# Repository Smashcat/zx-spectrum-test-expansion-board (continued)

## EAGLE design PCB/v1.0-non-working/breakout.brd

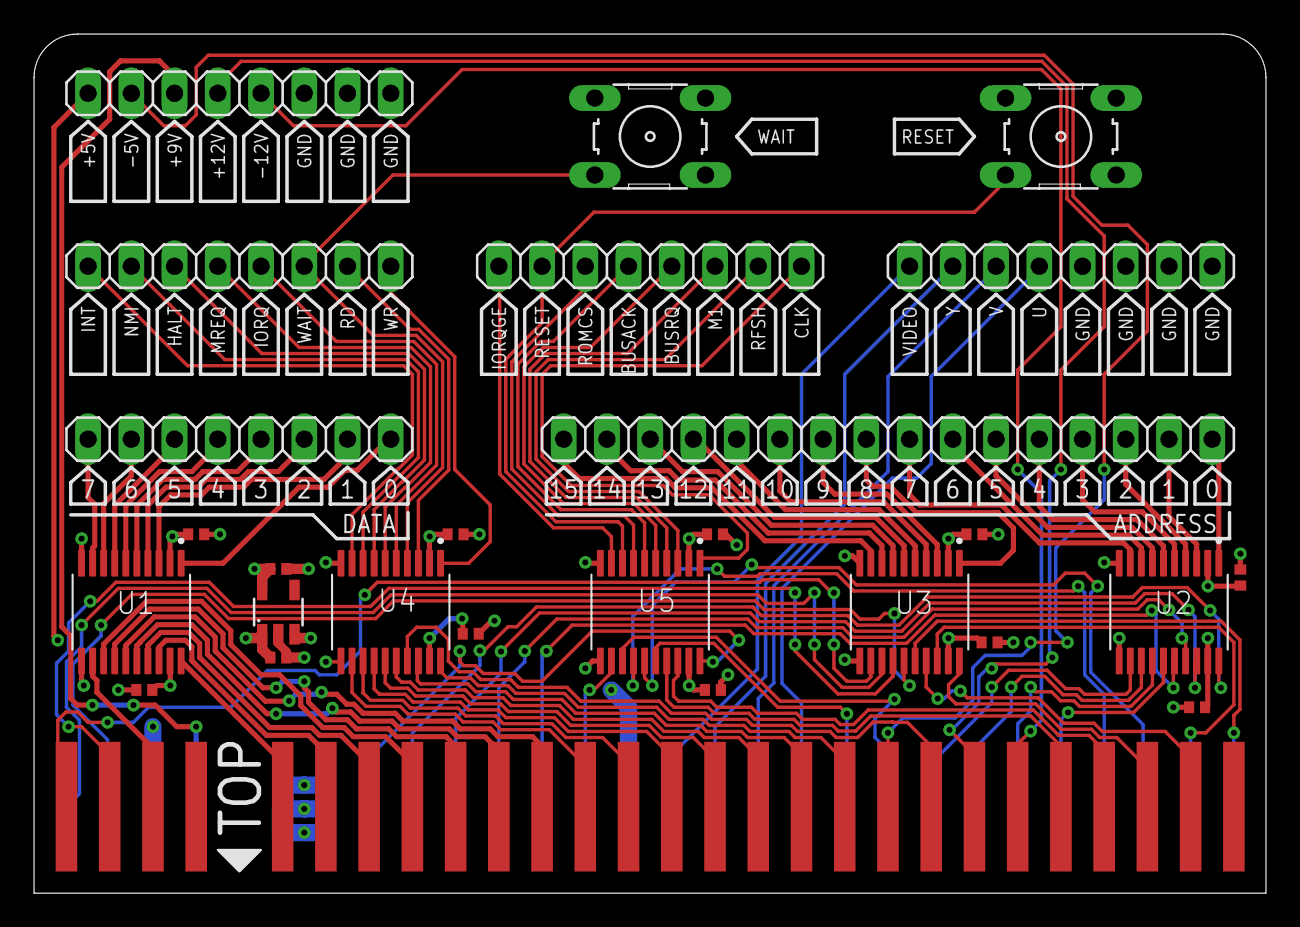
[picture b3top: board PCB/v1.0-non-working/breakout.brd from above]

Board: 4 copper layers, 72.4 x 50.5 mm, 27 parts (0 on the bottom side), 91 nets.

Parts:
3V3_REG4: 3V3; NCP718BSN330T1G
C1, C2, C3, C4, C5, C6, C7, C8, C9, C10: 100nF; C0402
C34, C35: 1uF; C0402
JP1, JP3, JP4, JP5, JP7: 1X08
JP2: 1X16
RESET_BUTTON: B3F-10XX-3D
U1, U2, U3, U4, U5: TXB0108PWR; SOP65P640X120-20N
U$1: ZX-SPECTRUM-EDGE-CONNECTOR
WAIT_BUTTON: B3F-10XX-3D

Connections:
3V3: 3V3_REG4.5, C1.1, C3.1, C5.1, C7.1, C9.1, C35.1, U1.2, U1.10, U2.2, U2.10, U3.2, U3.10, U4.2, U4.10, U5.2, U5.10
+5V: 3V3_REG4.1, 3V3_REG4.3, C2.1, C4.1, C6.1, C8.1, C10.1, C34.1, JP3.1, U1.19, U2.19, U3.19, U4.19, U5.19, U$1.B3
+9V: JP3.3, U$1.B4
+12V: JP3.4, U$1.A22
-5V: JP3.2, U$1.A20
-12V: JP3.5, U$1.A23
/BUSACK: U5.15, U$1.B26
/BUSACK_LOW: JP4.5, U5.6
/BUSRQ: U5.16, U$1.B19
/BUSRQ_LOW: JP4.4, U5.5
/HALT: U4.14, U$1.A15
/HALT_LOW: JP7.6, U4.7
/INT: U4.12, U$1.A13
/INT_LOW: JP7.8, U4.9
/IORQ: U4.16, U$1.A17
/IORQGE: U5.12, U$1.B13
/IORQGE_LOW: JP4.8, U5.9
/IORQ_LOW: JP7.4, U4.5
/M1: U5.17, U$1.A24
/M1_LOW: JP4.3, U5.4
/MREQ: U4.15, U$1.A16
/MREQ_LOW: JP7.5, U4.6
/NMI: U4.13, U$1.A14
/NMI_LOW: JP7.7, U4.8
/RD: U4.18, U$1.A18
/RD_LOW: JP7.2, U4.3
/RESET: U5.13, U$1.B20
/RESET_LOW: JP4.7, RESET_BUTTON.3, U5.8
/RFSH: U5.18, U$1.A25
/RFSH_LOW: JP4.2, U5.3
/ROMCS: U5.14, U$1.B25
/ROMCS_LOW: JP4.6, U5.7
/WAIT: U4.17, U$1.A21
/WAIT_LOW: JP7.3, U4.4, WAIT_BUTTON.3
/WR: U4.20, U$1.A19
/WR_LOW: JP7.1, U4.1
A0: U2.20, U$1.B9
A0_LOW: JP2.1, U2.1
A1: U2.18, U$1.B10
A1_LOW: JP2.2, U2.3
A2: U2.17, U$1.B11
A2_LOW: JP2.3, U2.4
A3: U2.16, U$1.B12
A3_LOW: JP2.4, U2.5
A4: U2.15, U$1.B24
A4_LOW: JP2.5, U2.6
A5: U2.14, U$1.B23
A5_LOW: JP2.6, U2.7
A6: U2.13, U$1.B22
A6_LOW: JP2.7, U2.8
A7: U2.12, U$1.B21
A7_LOW: JP2.8, U2.9
A8: U3.20, U$1.A26
A8_LOW: JP2.9, U3.1
A9: U3.18, U$1.B27
A9_LOW: JP2.10, U3.3
A10: U3.17, U$1.A27
A10_LOW: JP2.11, U3.4
A11: U3.16, U$1.B28
A11_LOW: JP2.12, U3.5
A12: U3.15, U$1.B2
A12_LOW: JP2.13, U3.6
A13: U3.14, U$1.A2
A13_LOW: JP2.14, U3.7
A14: U3.13, U$1.B1
A14_LOW: JP2.15, U3.8
A15: U3.12, U$1.A1
A15_LOW: JP2.16, U3.9
CLK: U5.20, U$1.B8
CLK_LOW: JP4.1, U5.1
D0: U1.20, U$1.A6
D0_LOW: JP1.1, U1.1
D1: U1.18, U$1.A7
D1_LOW: JP1.2, U1.3
D2: U1.17, U$1.A8
D2_LOW: JP1.3, U1.4
D3: U1.16, U$1.A11
D3_LOW: JP1.4, U1.5
D4: U1.15, U$1.A12
D4_LOW: JP1.5, U1.6
D5: U1.14, U$1.A10
D5_LOW: JP1.6, U1.7
D6: U1.13, U$1.A9
D6_LOW: JP1.7, U1.8
D7: U1.12, U$1.A3
D7_LOW: JP1.8, U1.9
GND: 3V3_REG4.2, C1.2, C2.2, C3.2, C4.2, C5.2, C6.2, C7.2, C8.2, C9.2, C10.2, C34.2, C35.2, JP3.6, JP3.7, JP3.8, JP5.5, JP5.6, JP5.7, JP5.8, RESET_BUTTON.1, U1.11, U2.11, U3.11, U4.11, U5.11, U$1.B6, U$1.B7, U$1.B14, WAIT_BUTTON.1
U: JP5.4, U$1.B18
V: JP5.3, U$1.B17
VIDEO: JP5.1, U$1.B15
Y: JP5.2, U$1.B16

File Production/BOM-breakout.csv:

Qty,Designator,Footprint,Comment,LCSC Part #,Description,Device
10,"C1, C2, C3, C4, C5, C6, C7, C8, C9, C10",C0402,100nF,C307331,"CAPACITOR, European symbol",C-EUC0402
2,"C34, C35",C0402,1uF,C52923,"CAPACITOR, European symbol",C-EUC0402
1,3V3_REG4,NCP718BSN330T1G,3V3,C587158,,NCP718BSN330T1G
5,"U1, U2, U3, U4, U5",SOP65P640X120-20N,TXB0108PWR,C17206,8-Bit Bidirectional Voltage-Level Shifter with Auto Direction Sensing and +/-15-kV ESD Protect 20-TSSOP -40 to 85  Check availability,TXB0108PWR

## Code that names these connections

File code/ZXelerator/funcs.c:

#include "funcs.h"
#include "resetData.h"

PIO pio;
uint addr_data_sm;

void setupIO(void){
        // -------------------------------
    // set-up user, romcs & reset gpio
    // -------------------------------
    gpio_init(PIN_RESET);
    gpio_set_dir(PIN_RESET,GPIO_OUT);
    gpio_put(PIN_RESET,false);    // initially not in RESET, as we need to wait for at least one memory access so that the PIO will work correctly
    //
    gpio_init(PIN_USER);
    gpio_set_dir(PIN_USER,GPIO_OUT);
    gpio_put(PIN_USER,true); // button active when connected to ground
    gpio_set_irq_enabled_with_callback(PIN_USER,GPIO_IRQ_EDGE_FALL,true,&resetButton);  // when user button pressed, interrupt code and run resetButton routine
    //
    gpio_init(PIN_ROMCS);
    gpio_set_dir(PIN_ROMCS,GPIO_OUT);
    gpio_put(PIN_ROMCS,false);    // start with ROM off  
    //
    gpio_init(PIN_LED);
    gpio_set_dir(PIN_LED,GPIO_OUT);
    gpio_put(PIN_LED,false);

    // Initialise the ASM data banks
    for(int n=0;n<3;n++){
        copyBank(ram[n][0],resetBank[0]);
    }
}

void setupPIO(void){
    // Set-up PIO
    pio=pio0;                                                           // use pio 0
    addr_data_sm=pio_claim_unused_sm(pio,true);                         // grab a free state machine from PIO 0
    uint addr_data_offset=pio_add_program(pio,&picoif2_program);        // get instruction memory offset for the loaded program
    pio_sm_config addr_data_config=picoif2_program_get_default_config(addr_data_offset); // get the default state machine config

    // set-up IN pins
    for(uint i=PIN_A0;i<PIN_A0+14;i++) {
        pio_gpio_init(pio,i);                                           // initialise all 14 input pins 
    }    
    pio_sm_set_consecutive_pindirs(pio,addr_data_sm,PIN_A0,14,false);   // input
    sm_config_set_in_pins(&addr_data_config,PIN_A0);                    // set IN pin base
    sm_config_set_in_shift(&addr_data_config,false,true,14);            // shift left 14 pins (A13-A0) into ISR, autopush resultant 32bit address to DMA RXF

    // set-up /ROMRQ pin
    pio_gpio_init(pio,PIN_ROMRQ);                                       // ROMRQ (OR of A14,A15 and /MREQ lines) When this switches to LOW it triggers the address line input DMA transfer
    pio_sm_set_consecutive_pindirs(pio,addr_data_sm,PIN_ROMRQ,1,false); // input
    
    // set-up OUT pins
    for(uint i=PIN_D0;i<PIN_D0+8;i++) {                                 // set-up OUT data pins
        pio_gpio_init(pio,i);                                           // initialise all 8 output pins
    }
    sm_config_set_out_pins(&addr_data_config,PIN_D0,8);                 // set OUT pin base & number (bits)
    sm_config_set_out_shift(&addr_data_config,true,true,8);             // right shift 8 bits of OSR to pins (D0-D7) with autopull on
    pio_sm_set_consecutive_pindirs(pio,addr_data_sm,PIN_D0,8,true);     // set all output pins to output, D0-D7
    pio_sm_init(pio,addr_data_sm,addr_data_offset,&addr_data_config);   // reset state machine and configure it

    // start PIO state machine
    pio_sm_set_enabled(pio,addr_data_sm,true);                          // enable state machine       
}

void releaseReset(void){
    busy_wait_us_32(50000);      // wait 50ms before lifting RESET          
    gpio_put(PIN_RESET,true);    // release RESET    
}

void __not_in_flash_func(handleZ80Read)(void){
    uint32_t bank1SwapCnt=0;
    uint32_t keyScanCnt=0;
    uint32_t currentSubBank=0;
    int haltCD=0;
    const uint8_t *readPtr=ram[readBank][currentSubBank];
    
    enableROMOutput();
    gpio_put(PIN_RESET,true);   // lift reset
    while(true){
        while((pio->fstat & (1u << (PIO_FSTAT_RXEMPTY_LSB + addr_data_sm))) != 0);
        uint32_t address=pio->rxf[addr_data_sm];
        //uint32_t address=pio_sm_get_blocking(pio,addr_data_sm);
        pio->txf[addr_data_sm] = *(readPtr+address);
        //pio_sm_put_blocking(pio,addr_data_sm,*(readPtr+address)); // if ROMCS off then direction of Data chip is input so they do not interfere
        writeOK=1;
        if((address==0x3fff) && (keyScanCnt==0)) {       // Z80 is about to send 8 scan codes from keys
            keyScanCnt=8;

        // When sending keyboard scan codes, the high byte of the address will be 0x3f, and the low byte will be the data
        }else if(keyScanCnt>0){
            
            if((address>>8)==0x3f){
                --keyScanCnt;
                keyboardScan[keyScanCnt]=(~(uint8_t)(address&0xff))&0x1f;
            }

        // Z80 is about to read the first bank, for the top half of the screen (chasing the beam) - this is just before the halt instruction, so there is plenty of time to flip buffers
        }else if(address==0x3ffe){  
            haltCD=2;
        }else if(haltCD>0){

            if(--haltCD==0){
                currentSubBank=0;
                
                if(flipBank){
                    if(++readBank==2){
                        readBank=0;
                    }
                    if(++writeBank==2){
                        writeBank=0;
                    }
                }
                
                readPtr=ram[readBank][currentSubBank];
                ++frameDisplayed;
                flipBank=0;
                __dsb();   // Ensure write completes before waking other core
                __sev();   // Send event to wake core1 out of __wfe()
            }

        // Z80 is about to read the second bank, for the bottom half of the screen (racing the beam)
        }else if(address==0x3ffd){  
            bank1SwapCnt=3; // We allow 3 more memory reads before swapping the bank, so the Z80 can read in the jump instruction following the request to swap banks
        }else if(bank1SwapCnt>0){
            if(--bank1SwapCnt==0){
                currentSubBank=1;
                readPtr=ram[readBank][currentSubBank];
            }
        }else if(address>0xffff){
            break;
        }

    }
    eroneousAddr=1;
}

//
// ---------------------------------------------------------------------------
// resetButton - interrupt driven routine when user button pressed
// input:
//   gpio - which gpio called this routine
//   events - the compressed storage
// ---------------------------------------------------------------------------
void resetButton(uint gpio,uint32_t events) {
    uint32_t address;         
    busy_wait_us_32(100000);    // litle wait to help with button bounce
    gpio_put(PIN_RESET,false); // put Spectrum in RESET state                      
    // wait for button release and check held for 1second to switch ROM otherwise just reset
    uint64_t lastPing=time_us_64();        
    do {
        busy_wait_us_32(100000); // wait 100ms between each read, minimum 200ms wait on each press
    } while((gpio_get(PIN_USER)==false)&&(time_us_64()<lastPing+1000000));
    // button pressed for >=1second?
    if(time_us_64()>=lastPing+1000000) {                                              
        gpio_put(PIN_ROMCS,true);     // turn on ROMCS  
        gpio_put(PIN_LED,true);          
    }
    busy_wait_us_32(100000);    // wait 100ms before lifting RESET       
    gpio_put(PIN_RESET,true);   // lift reset    
}

void enableROMOutput(void){
    //gpio_put(PIN_RESET,true);   // release reset    
    //busy_wait_ms(2800);    // wait 1000ms before lifting RESET           
    gpio_put(PIN_RESET,false);   // set reset    
    gpio_put(PIN_ROMCS,true);   // turn on ROMCS  
    busy_wait_ms(800);    // wait 1000ms before lifting RESET           
}

void copyBank(uint8_t *dest, const uint8_t *src){
    memcpy(dest, src, 0x2f00*2);
}

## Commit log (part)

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2024-09-14 Added images
2024-09-14 README update
2024-09-14 Added link to JLCPCB
2024-09-15 Added some more text about production
2024-10-05 2nd version of board, with no level translation for now, to test if Pico can reliably send data back at 3.3v (it is 5V tolerant for reading address/data bus)
2025-03-02 Added some initial test code for full screen updates - unfinished
2025-03-03 Ongoing dev
2025-03-04 Added z80 manual, plus updated test code so now does perfect 25fps updates, plus plays 2 tones per update from 2 different buffers - these will need to reside in the cartridge address space so ARM co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
2025-03-06 Added some docs about bi-color timing, sped up test code a bit
2025-03-07 Trying out bi-color with full screen updates - might use too much ROM...
2025-03-08 Finished bi-colour code for even frames!
2025-03-10 Checked in docs, more testing and optimisation. Looks like last 16 rows will be unable to scroll around smoothly as they'll be 1/25th second delayed from the rest of the screen. A bit annoying, but c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
2025-03-14 Checked in initial RP2350 code
2025-03-14 Clean up
2025-03-14 Added vscode config
2025-03-15 Paranoid save, as I'm making good progress on optimising the rendering code!
2025-03-16 Fully optimised renderer, fixed clock code index counting, so I can index the positions of screen bytes and attributes from MCU buffers
2025-03-16 Further optimisations, also switched to 16 byte blits to make mapping buffer to display list commands simpler!
2025-03-17 More updates, code almost ready to put into firmware
2025-03-17 Success! MCU is now working as the ROM, handling data from the Z80, to swap buffer code, and image is rock steady!
2025-03-21 Added first iteration of code offset arrays to update the display data from the C code on MCU
2025-03-22 Working on dynamically updating the ASM
2025-03-23 Debugging underway
2025-03-25 New images
2025-03-25 Created initial BOM and mount files, although need to replace one of the octal buffers with a level shifter
2025-03-28 Fixed hardware issue! Fixed firmware issue with volatiles not updating - core1 was not starting up!
2025-03-29 Fixed bugs! Moved some code to RAM, also tried moving some const data from flash to RAM (removing const), seemed to completely fix random crashes caused by cache misses, forcing contention on the QSP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
2025-03-30 Now have some sprites moving!
2025-03-31 Added layer code, not yet fully working. Added web script for sprite/tile conversion, added test images etc
2025-04-01 partially implemented tile layers - need to fix attribute glitch in bytes 8,9 and 16,17, and handle vscroll and hscroll offsets
2025-04-02 Tile layers now mask correctly, and can scroll vertically and move attributes to match.
2025-04-02 Layers now scrolling in all directions nicely! Demo now also showing keyboard input
2025-04-04 Trying to resolve occaasional glitch in returning data from a memory request from Z80, caused by (I assume) a cache miss. Removed calls from core1 loop into non RAM-based functions, to hopefully keep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
2025-04-05 Sprites can now have colour! Code on core1 appears to be completely stable now - ran for hours with multiple layers+sprites with zero glitches
2025-04-06 Sprites can now be various sizes, inputDevice functions added, so keyboard/joystick input is now simpler, plus can show the actual key name is needed. Cleaned up code, moved engine functions into sub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
2025-04-07 Added some test artwork (not yet in use), completed particle system! Next stage is adding ability to blit a large bitmap directly to render buffer, to use under tile/sprite/particle layers
2025-04-09 New cartridge PCB design, smaller, using RP2350 now. Need to modify more to reduce wings on side, so it's square I think - will give more space in casing
2025-04-09 PCB design completed and submitted for production
2025-04-10 Added ability to properly use bi-color ASM output from zx paint, to use as splash screen when ROM starts up - it's the image that's embedded in the actual ASM skeleton
2025-04-20 New version of IF2 cart, fixed bug
2025-04-20 Finished redesign of IF2 PCB - all data and address tracks now length matched, although whether that makes any difference... Submitted for production
2025-04-22 Scaled sprites working
2025-04-23 Ongoing dev to add bitmap layer type
2025-04-24 New logo finished, also web convertor script to strip out extraneous ATTR data, from 32x192 to 32x48
2025-05-05 Fixed issue with attr updating before bitmap in ASM output, added bitmap layer scrolling (only by bytes in X axis currently)
2025-05-06 Bitmap layers working, with smooth scrolling, sprites now use centre for x,y positioning, to make scaling easier to handle - game intro screens started
2025-05-07 Lots of new graphics, completed bit bitmap layer code bug fixing etc. Title screen coming along
2025-05-08 More of title screen animations working
2025-05-25 Final(?) design of IF2 PCB.
